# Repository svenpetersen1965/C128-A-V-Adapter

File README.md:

# C128-A-V-Adapter
An A/V-adaptor board for the Commodore C128. This board is intended to connect to the Commodore C128 and use standard cables (audio, composite with RCA connector and/or s-video with a mini-DIN cable).

It also provides a 330Ohm resistor, which attenuates the s-video chroma line. This resistor can be bridged with a jumper.

Also an optional stereo output on pin 7 of the a/v jack (stereo sid, FPGA SID etc.) can be connected to the right audio channel. By default, this channel is also connected to the (mono) audio output.

# Rev. 1
This revision was required due to the obsolescence of the Lumberg BTOR1 RCA jacks. CUI Inc. RCJ-02* type conectors are used now. There are alternative RCA jacks from Keystone, which fit the same footprint (see BOM). Because of the new layout, a new case was required, too. There are recessions on the bottom shell for the solder pads, which have chancged in this board revision.

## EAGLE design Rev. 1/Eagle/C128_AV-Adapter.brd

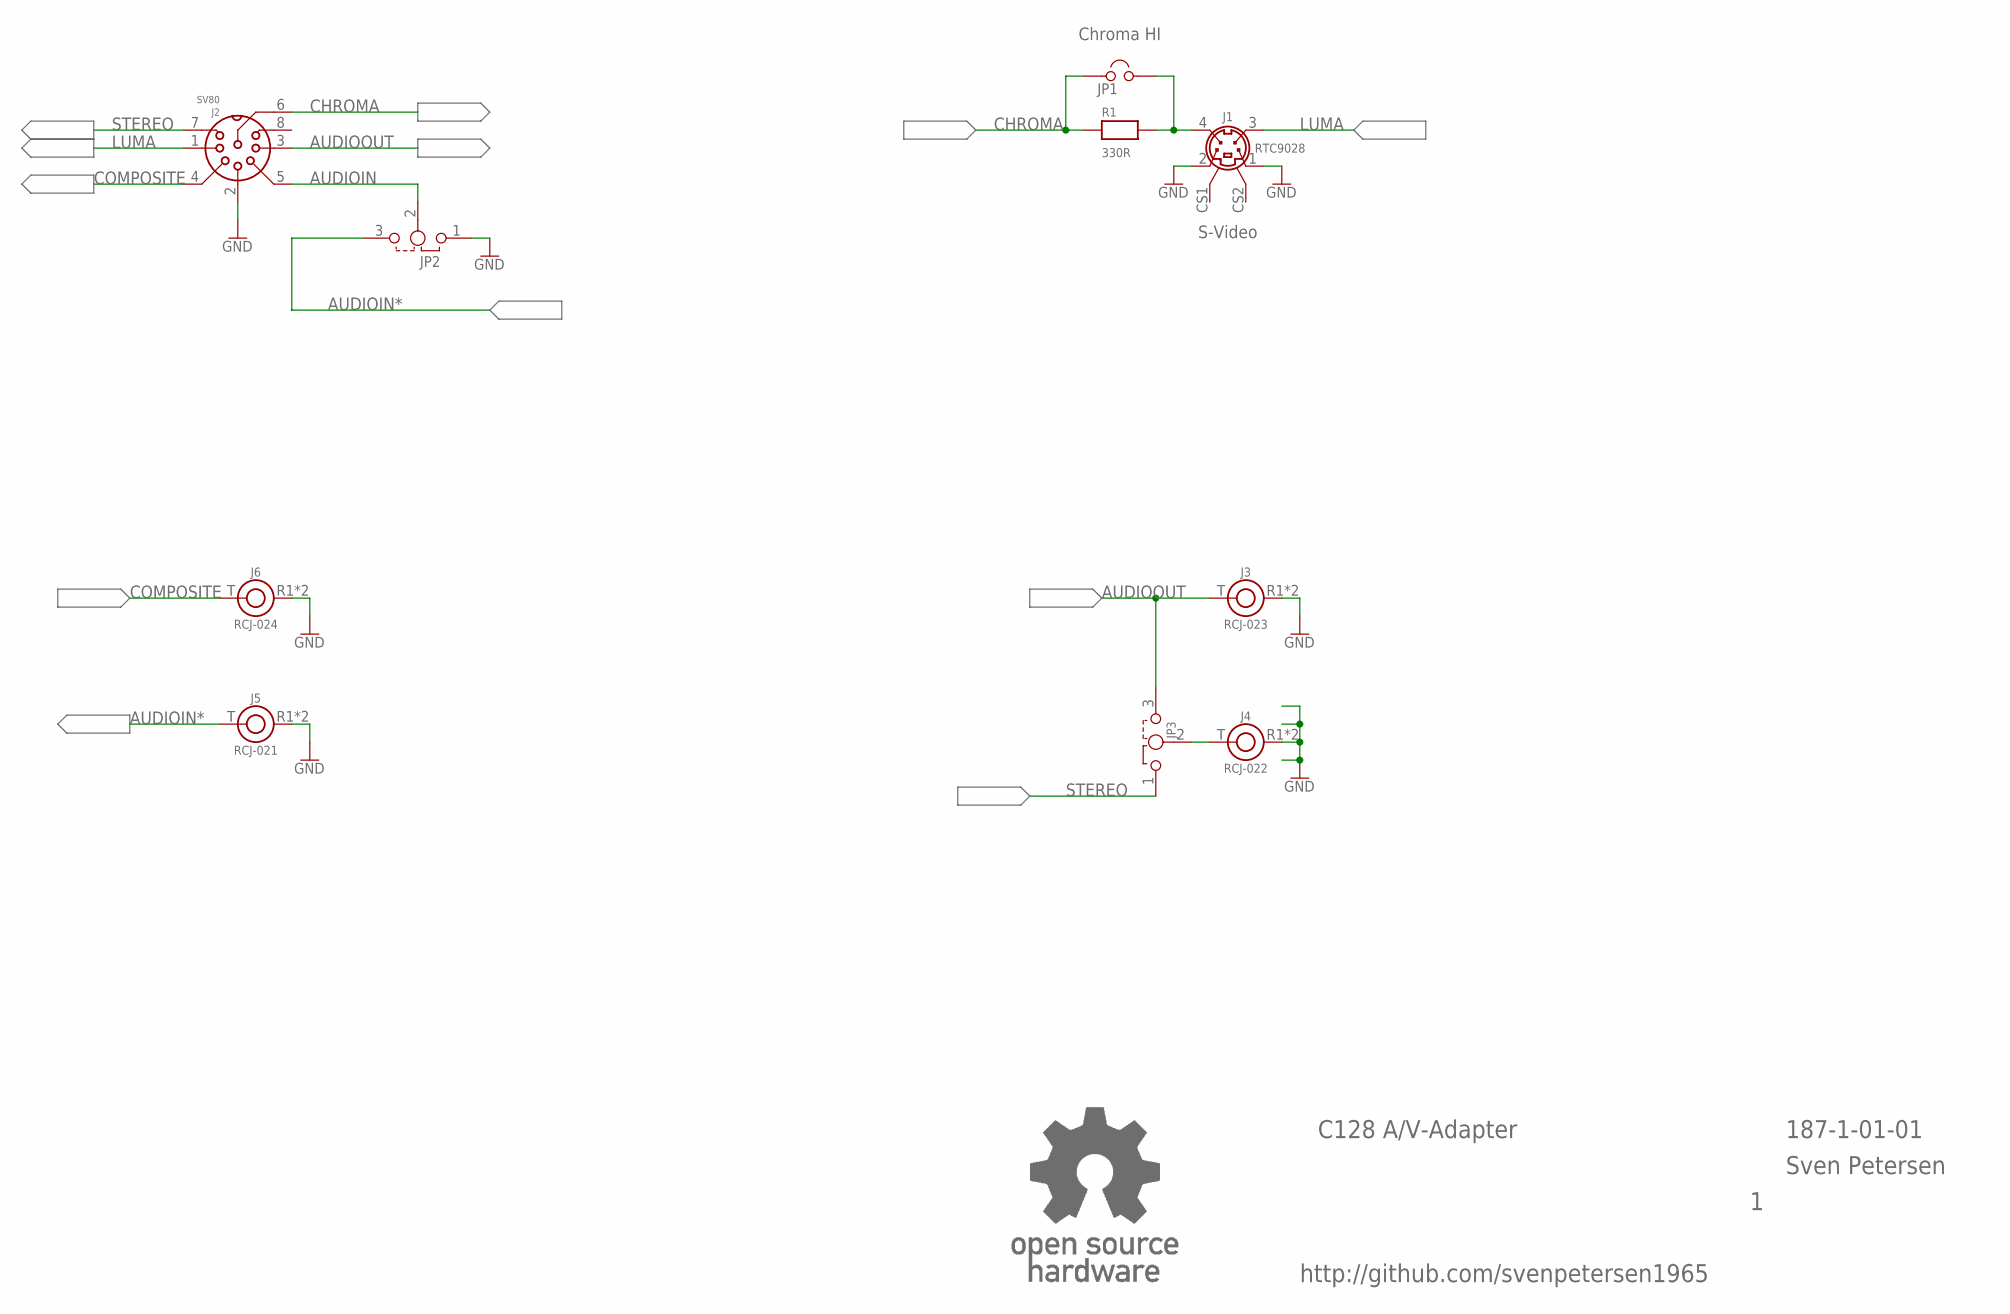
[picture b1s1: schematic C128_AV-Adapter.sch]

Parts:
J1: RTC9028; MINIDIN4_V
J2: SV80; SV80_INNER
J3: RCJ-023; RCJ-02X
J4: RCJ-022; RCJ-02X
J5: RCJ-021; RCJ-02X
J6: RCJ-024; RCJ-02X
JP1: JUMPER; 1X02
JP2, JP3: DJUMPER; 1X03
R1: 330R; R-10
U$25: OPEN_SOURCE_HW; OPENHW

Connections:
AUDIOIN: J2.5, JP2.2
AUDIOIN*: J5.T, JP2.3
AUDIOOUT: J2.3, J3.T, JP3.3
AUDIOR: J4.T, JP3.2
CHROMA: J2.6, JP1.1, R1.1
COMPOSITE: J2.4, J6.T
GND: J1.1, J1.2, J2.2, J3.R1 (R), J3.R2 (R), J4.R1 (R), J4.R2 (R), J5.R1 (R), J5.R2 (R), J6.R1 (R), J6.R2 (R), JP2.1
LUMA: J1.3, J2.1
unnamed: J1.4, JP1.2, R1.2
STEREO: J2.7, JP3.1

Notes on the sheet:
C128 A/V-Adapter
187-1-01-01
Sven Petersen
http://github.com/svenpetersen1965
Chroma HI
S-Video

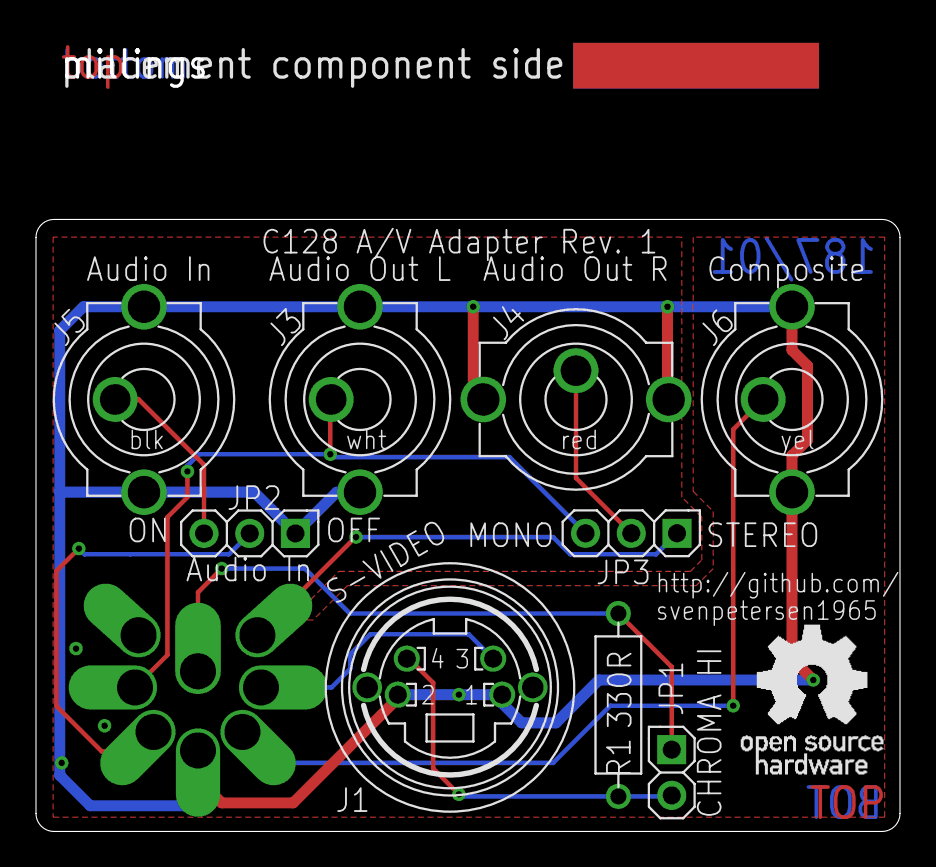
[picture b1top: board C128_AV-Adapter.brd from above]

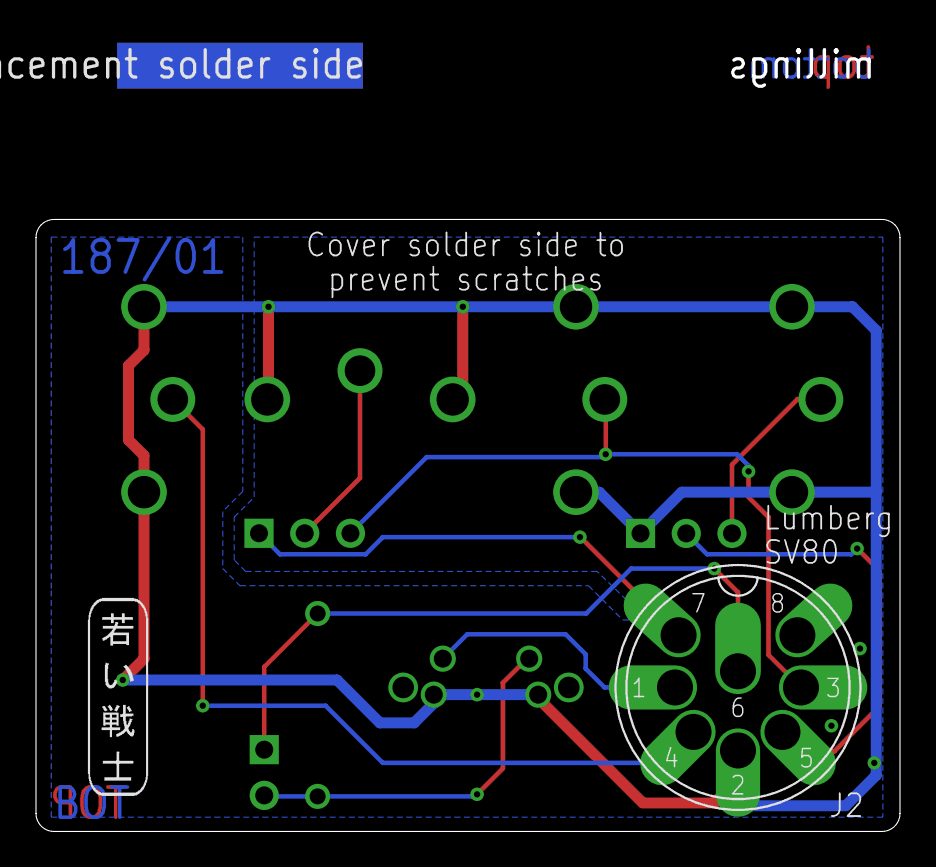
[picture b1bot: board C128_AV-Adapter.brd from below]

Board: 2 copper layers, 48.0 x 44.2 mm, 14 parts (2 on the bottom side), 10 nets.

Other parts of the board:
U$22: 2LAYER
U$23: SVEN_TAG
U$24: PCB-TITLE/

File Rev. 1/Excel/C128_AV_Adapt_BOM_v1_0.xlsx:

C128 A/V-Adaptor Rev. 1
Bill of Material Rev. 1.0
Pos. | Qty | Value | Footprint | Ref.-No. | Comment
1 | 1 | 187-2-01-01 | 2 Layer | PCB Rev. 1 | 2 layer, Cu 35µ, HASL, 48.0mm x 34.0mm, 1.6mm FR4
2 | 2 | 1x 3p pin header, pitch 2.54mm | 1X03 | JP2, JP3 | standard pin header, e.g. Reichelt RND 205-00624,
3 | 1 | 1x 2p pin header, pitch 2.54mm | 1X02 | JP1 | standard pin header, e.g. Reichelt RND 205-00623
4 | 3 | Jumper 2.54mm pitch | jumper | (JP1), (JP2), (JP3) | Jumper (0,1") with holder/latch, e.g. tme.eu: JUMPER-H/B, Farnell: 2396301, New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
5 | 1 | 330R | R-10 | R1 | resistor, 0.25W or more, 5% or better.
6 | 1 | RCJ-021 | RCJ-02X | J5 | CUI Inc., RCA jack, vertical, black. Mouser: 490-RCJ-021, Digikey: CP-1406-ND. 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
7 | 1 | RCJ-022 | RCJ-02X | J4 | CUI Inc., RCA jack, vertical, red. Mouser: 490-RCJ-022, Digikey: CP-1407-ND. Al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
8 | 1 | RCJ-023 | RCJ-02X | J3 | CUI Inc., RCA jack, vertical, white. Mouser: 490-RCJ-023, Digikey: CP-1408-ND. 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
9 | 1 | RCJ-024 | RCJ-02X | J6 | CUI Inc., RCA jack, vertical, yellow. Mouser: 490-RCJ-024, Digikey: CP-1409-ND.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
10 | 1 | RTC9028 | MINIDIN4_V | J1 | Mini-DIN, 4p, vertical. E.g. AliExpress:
 |  |  |  |  | RTConnector: RTC9028
 |  |  |  |  | ebay.de
11 | 1 | SV80 | SV80_INNER | J2 | Inner part of Lumberg 033099 SV 80, e.G. Reichelt: LUM SV 80, Newark: 23AH4043,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

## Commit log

2021-12-22 Initial release
2022-02-26 Gerbers removed
2022-11-09 Rev. 1 released
    In Rev. 1, the obsolete Lumberg BTOR1 RCA jacks are replaced with CUI Inc. connectors.
2022-11-09 Case Rev. 1 released
    The PCB Rev. 1 requires a different case. The label stays the same.
